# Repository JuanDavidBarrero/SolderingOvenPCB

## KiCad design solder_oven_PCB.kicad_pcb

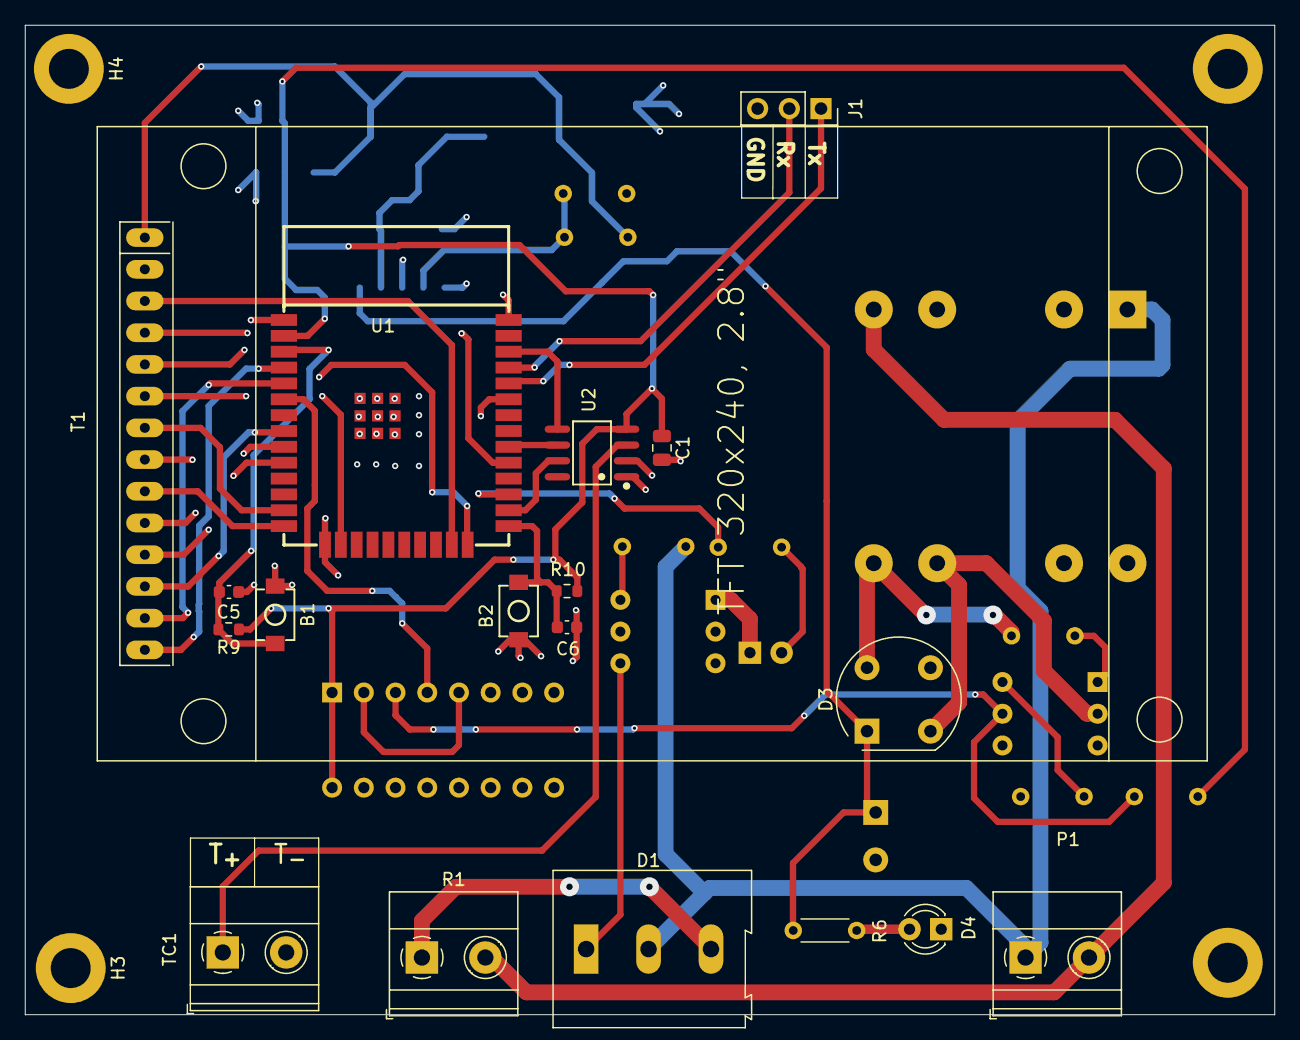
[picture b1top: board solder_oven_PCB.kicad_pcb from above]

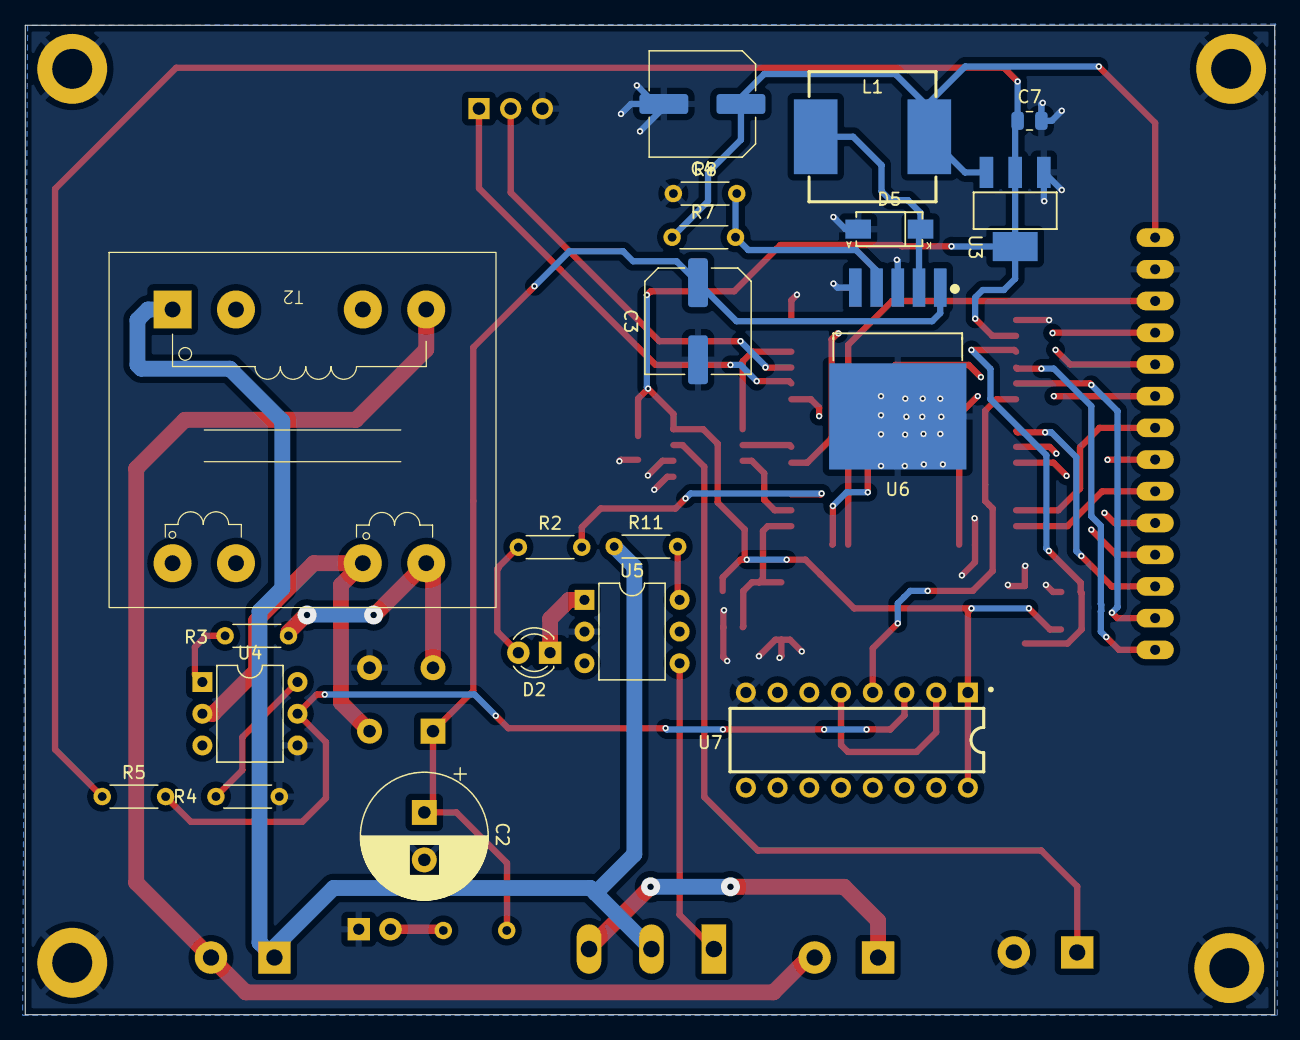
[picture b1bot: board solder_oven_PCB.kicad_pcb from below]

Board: 4 copper layers, 100.1 x 79.2 mm, 42 parts (20 on the bottom side), 42 nets.

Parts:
B1, B2: SW-SMD_L3.9-W2.9-LS4.8
C1, C7: 100nF; C_0805_2012Metric
C2: 1000uF; CP_Radial_D10.0mm_P3.80mm
C3: 470uF; C_Elec_8x6.2
C4: 220uF; C_Elec_8x6.2
C5, C6: 100nF; C_0603_1608Metric
D1: Generic_Triac_A1A2G; TerminalBlock_Altech_AK300-3_P5.00mm
D2, D4: LED; LED_D3.0mm
D3: W10G; Diode_Bridge_Round_D9.8mm
D5: SMA_L4.4-W2.8-LS5.4-R-RD
H1, H2, H3, H4: M3 screw; MountingHole_3.2mm_M3_DIN965_Pad
J1: UART; PinSocket_1x03_P2.54mm_Vertical
L1: IND-SMD_L10.3-W10.3_1274AS-H-330M
P1: Conn_WallPlug; TerminalBlock_Phoenix_MKDS-1,5-2-5.08_1x02_P5.08mm_Horizont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
R1: Heater; TerminalBlock_Phoenix_MKDS-1,5-2-5.08_1x02_P5.08mm_Horizont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
R2: 220; R_Axial_DIN0204_L3.6mm_D1.6mm_P5.08mm_Horizontal
R3, R11: 1K; R_Axial_DIN0204_L3.6mm_D1.6mm_P5.08mm_Horizontal
R4: 1M; R_Axial_DIN0204_L3.6mm_D1.6mm_P5.08mm_Horizontal
R5, R6, R7: 10K; R_Axial_DIN0204_L3.6mm_D1.6mm_P5.08mm_Horizontal
R8: 3.3K; R_Axial_DIN0204_L3.6mm_D1.6mm_P5.08mm_Horizontal
R9, R10: 3.3K; R_0603_1608Metric
T1: TFT-320x240
T2: AT-010-V
TC1: Thermocouple; TerminalBlock_Phoenix_MKDS-1,5-2-5.08_1x02_P5.08mm_Horizont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
U1: WIFI-SMD_ESP32-WROOM-32E
U2: SOIC-8_L4.9-W3.9-P1.27-LS6.0-BL
U3: SOT-223-3_L6.5-W3.4-P2.30-LS7.0-BR
U4: H11AA1; DIP-6_W7.62mm
U5: MOC3052M; DIP-6_W7.62mm
U6: TO-263-5_L10.2-W8.9-P1.70-BR
U7: DIP-16_L20.3-W10.2-P2.54-LS10.2-BL

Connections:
12_{NN}: D3.2, T2.7, U4.2
12_{V_{ac}}: D3.4, R3.1, T2.6
+3.3V: C1.1, C7.1, R5.1, R9.1, R10.1, U1.2 (3V3), U2.4 (VCC), U3.2 (VOUT), U3.4 (VOUT), U7.1 (Vcc), U7.16 (VDD)
+5V: C4.1, L1.2, R7.2, T1.1 (VCC), U3.3 (VIN)
+12v: C2.1, C3.1, D3.1 (+), R6.2, U6.1 (VIN)
/Zero_Cross: U1.6 (IO34), U7.4 (NotB)
/esp32/Boot: B2.2, C6.1, R10.2, U1.25 (IO0)
/esp32/CLK: T1.7 (SCK), U1.13 (IO14)
/esp32/CS: T1.3 (CS), U1.23 (IO15)
/esp32/CS_{T}: U1.30 (IO18), U2.6 (~CS)
/esp32/D0: U1.26 (IO4), U2.7 (SO)
/esp32/D/C: T1.5 (DC), U1.24 (IO2)
/esp32/EN: B1.2, C5.1, R9.2, U1.3 (EN)
/esp32/LED: T1.8 (LED), U1.33 (IO21)
/esp32/MISO: T1.9 (MISO), U1.14 (IO12)
/esp32/MOSI: T1.6 (MOSI), U1.16 (IO13)
/esp32/RST: T1.4 (RST), U1.29 (IO5)
/esp32/Rx: J1.2, U1.35 (TXD0)
/esp32/SCK: U1.36 (IO22), U2.5 (SCK)
/esp32/T_CLK: T1.10 (T_CLK), U1.10 (IO25)
/esp32/T_CS: T1.11 (T_CS), U1.9 (IO33)
/esp32/T_DIN: T1.12 (T_DIN), U1.8 (IO32)
/esp32/T_DO: T1.13 (T_DO), U1.5 (SENSOR_VN)
/esp32/T_IRQ: T1.14 (T_IRQ), U1.4 (SENSOR_VP)
/esp32/Tx: J1.1, U1.34 (RXD0)
/modules/shot: D1.3 (G), U5.4
/trigger_Gate: R2.2, U1.27 (IO16)
Fase: D1.2 (A2), P1.1 (AC_P), R11.1, T2.1
GND: B1.1, B2.1, C1.2, C2.2, C3.2, C4.2, C5.2, C6.2, C7.2, D3.3 (-), D4.1 (K), D5.1, H1.1, H2.1, H3.1, H4.1, J1.3, R4.2, R8.1, T1.2 (GND), TC1.2 (-), U1.1 (GND), U1.15 (GND), U1.38 (GND), U1.39 (GND), U2.1 (GND), U2.2 (T-), U3.1 (GND), U4.4, U5.2, U6.3 (GND), U6.5 (~ON/OFF), U7.8 (VSS)
unnamed: D1.1 (A1), R1.1
unnamed: D2.2 (A), R2.1
unnamed: D2.1 (K), U5.1
unnamed: D4.2 (A), R6.1
unnamed: R3.2, U4.1
unnamed: R4.1, U4.6
unnamed: R11.2, U5.6
unnamed: TC1.1 (+), U2.3 (T+)
unnamed: R7.1, R8.2, U6.4 (FB)
unnamed: D5.2, L1.1, U6.2 (OUT)
unnamed: R5.2, U4.5, U7.3 (A)
unnamed: U7.2 (NotA), U7.5 (B)
Neutro: P1.2 (AC_N), R1.2, T2.5

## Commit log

2024-08-25 init: the project begin
2024-08-27 update: the schematic is complete but is not order
2024-08-31 update: now the pcb has sheets and pcb layout
2024-09-02 update: pcb with component in place
2024-09-06 update: pcb almost done
2024-09-27 update: gerbers generator
